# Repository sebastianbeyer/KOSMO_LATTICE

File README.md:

## KOSMO format adoption from Mutable Instruments Grids

Using the Schematic of Mutable Instruments and initial Kicad files by www.quinie.nl

I had to fix the pot direction and the button but now it works!
Remember to adjust the LED resistors (`R37, R38, R39`) to the LEDs your are using!
For the firmware I have added the compiled firmware (`grids.hex`) and a script on how to upload it to your nano (`upload.sh`, you need to adjust the paths)

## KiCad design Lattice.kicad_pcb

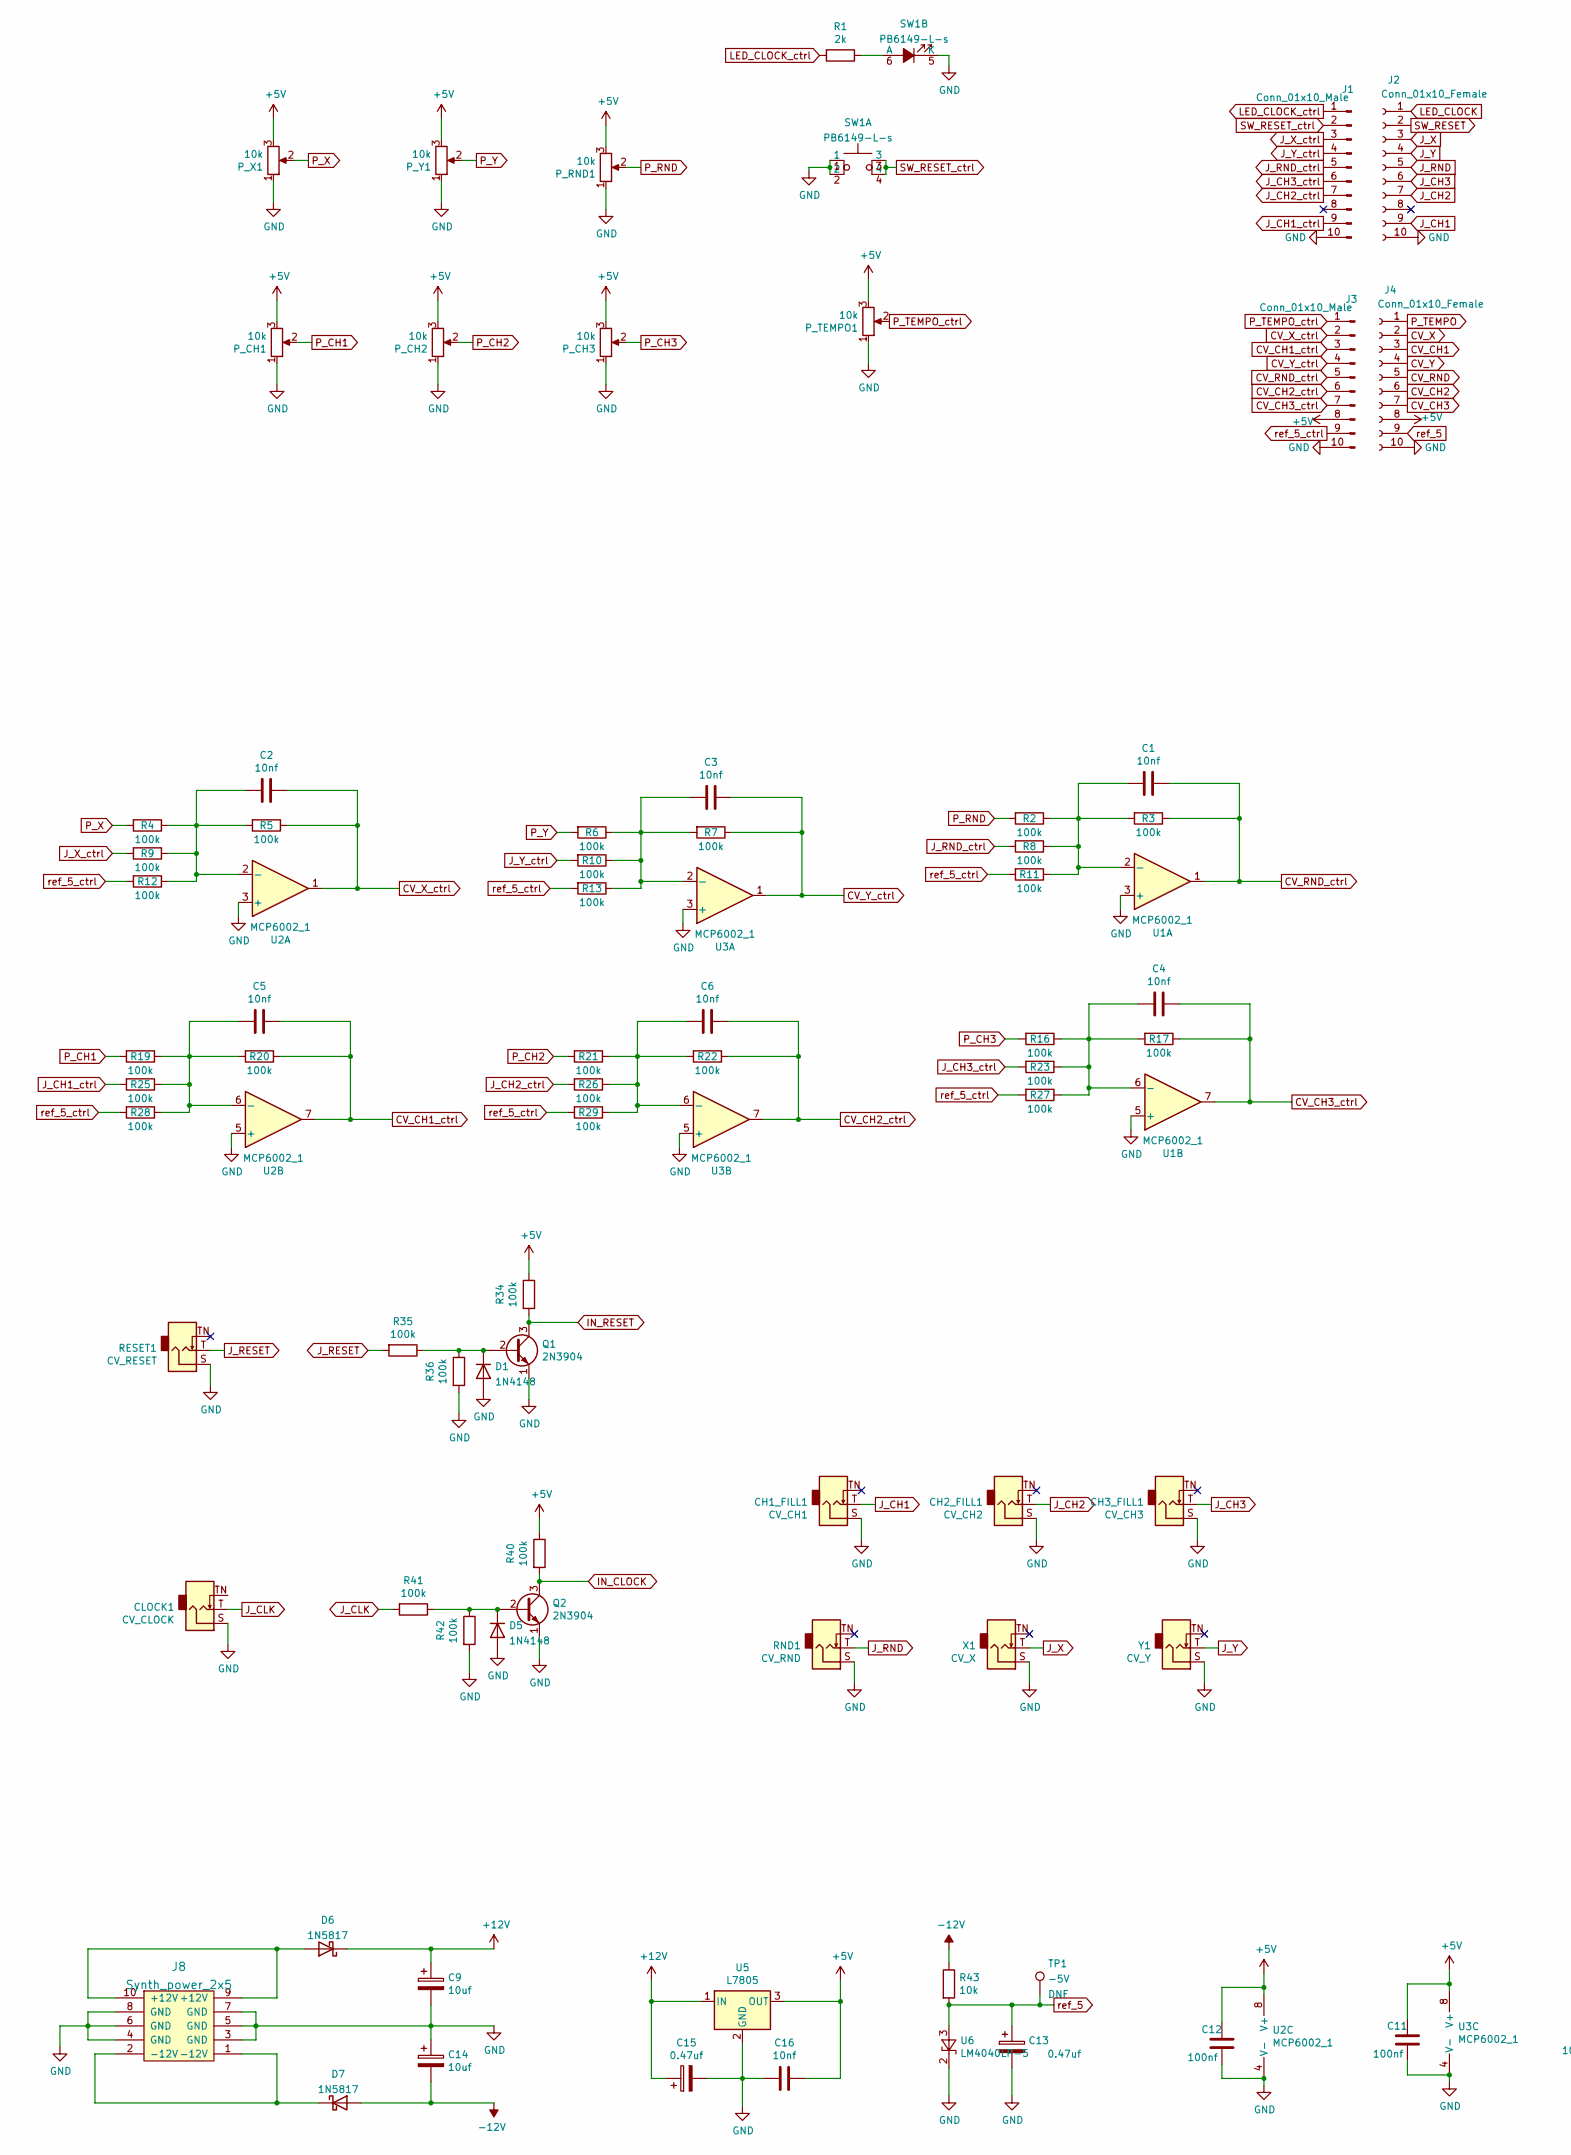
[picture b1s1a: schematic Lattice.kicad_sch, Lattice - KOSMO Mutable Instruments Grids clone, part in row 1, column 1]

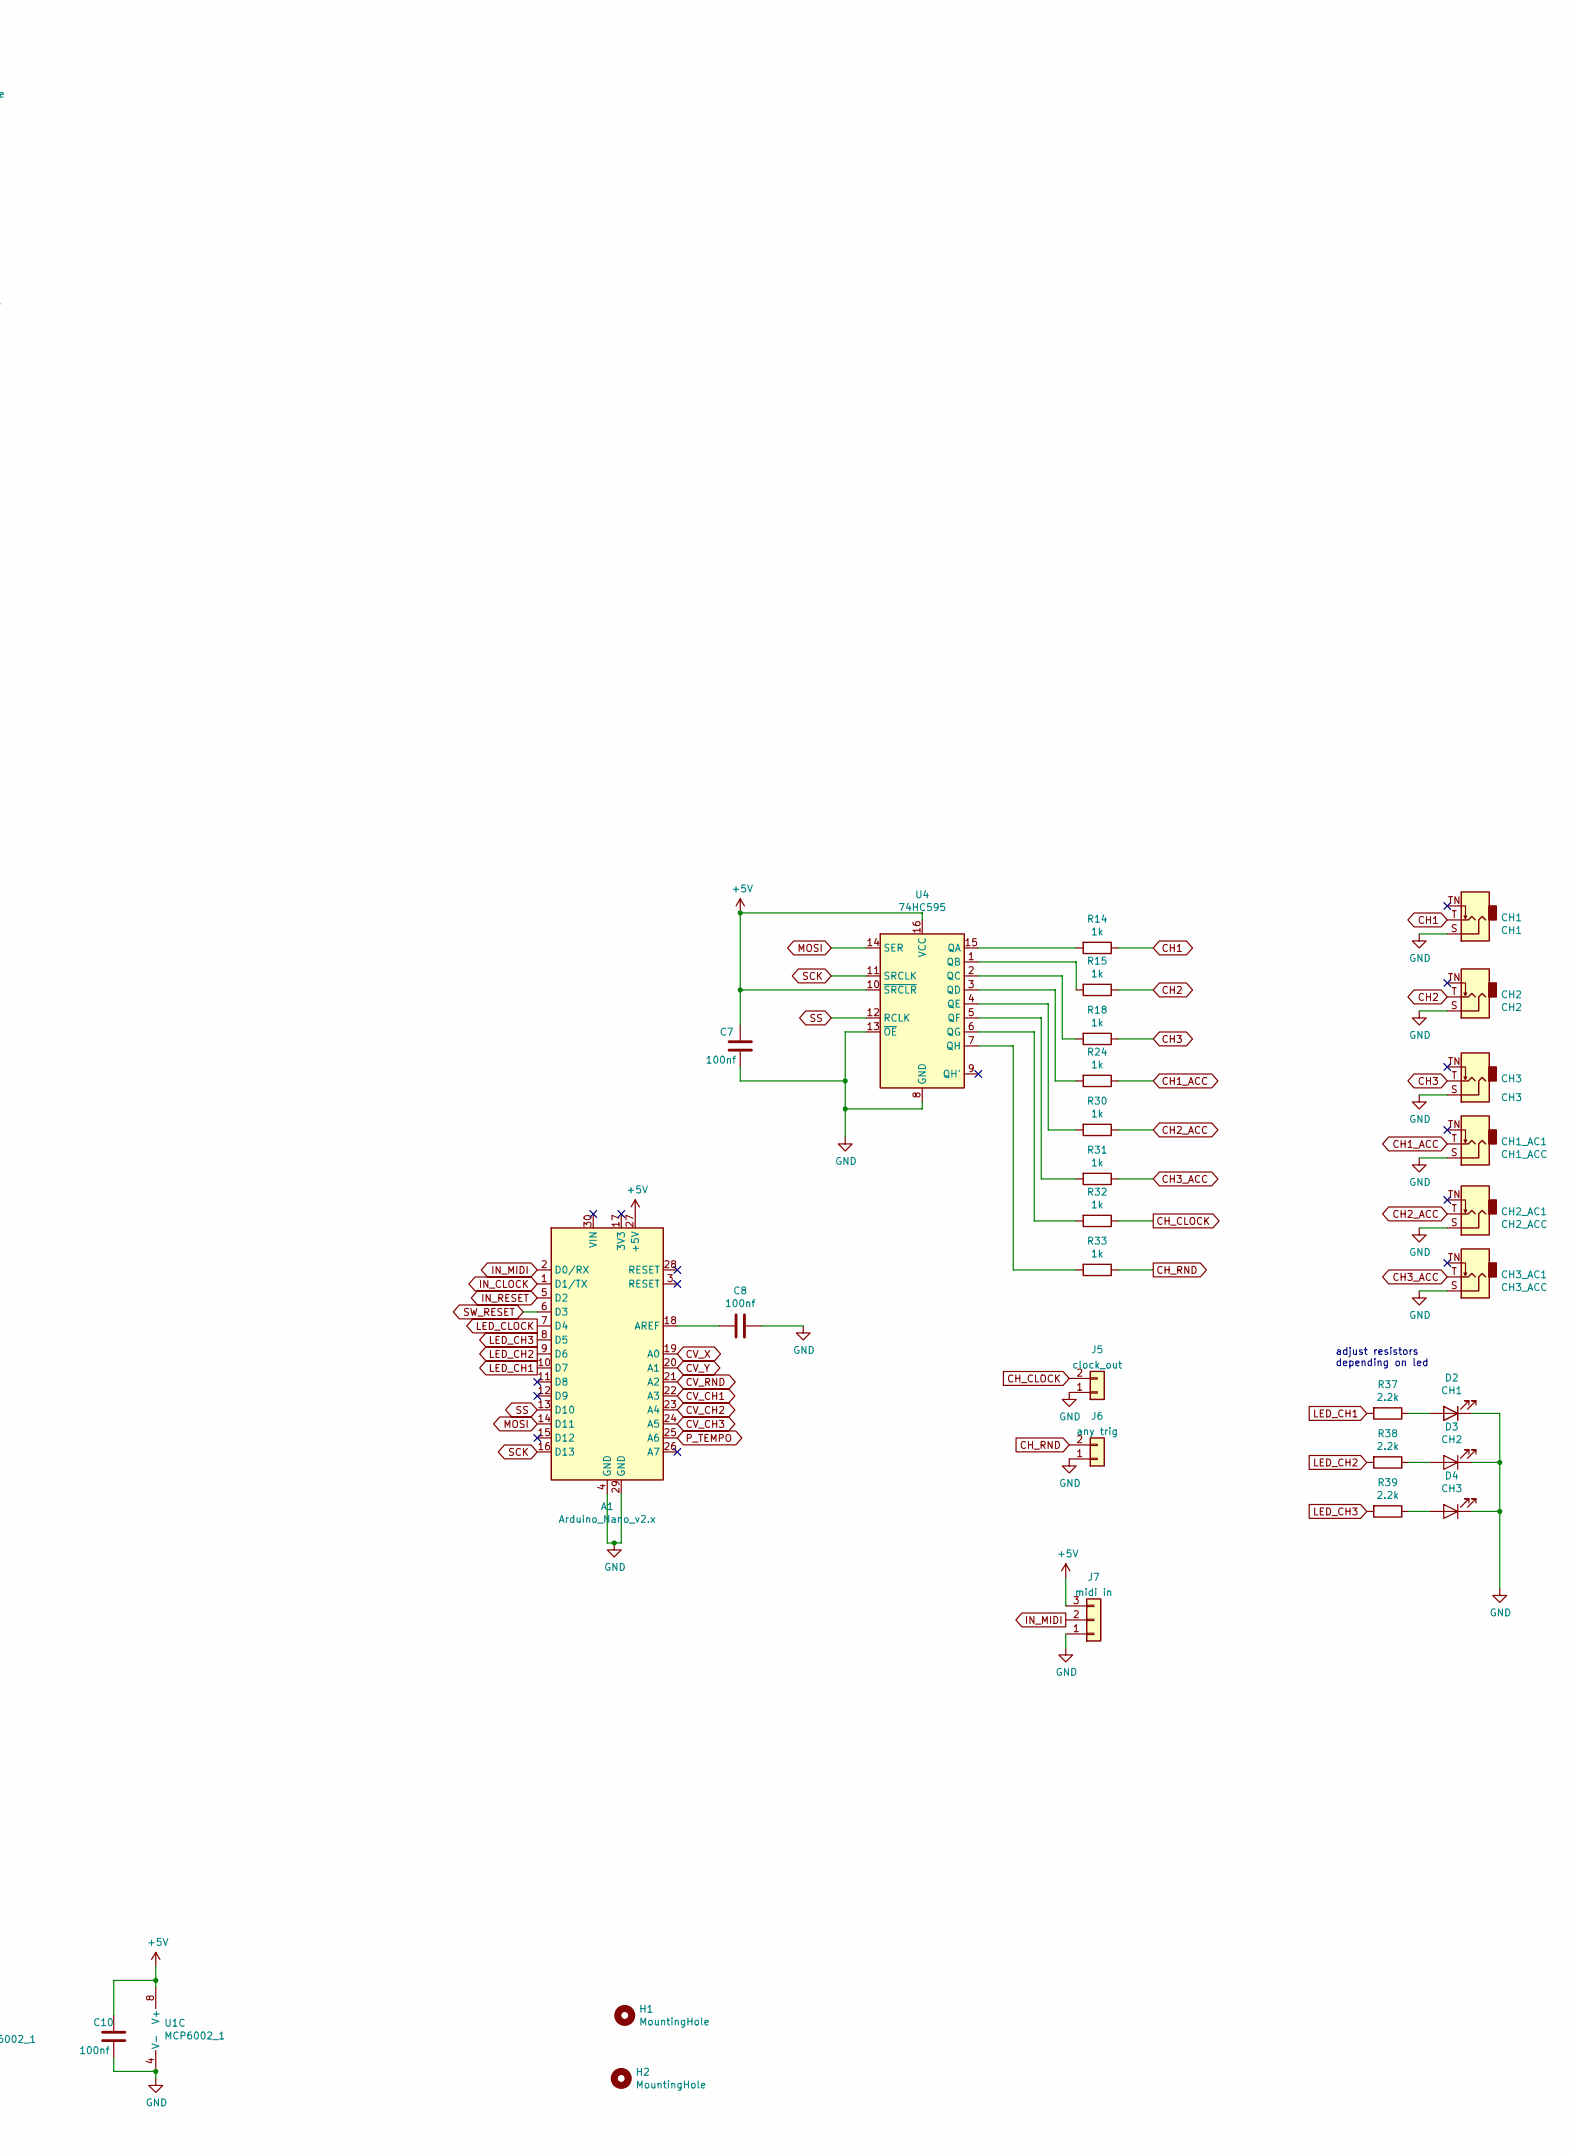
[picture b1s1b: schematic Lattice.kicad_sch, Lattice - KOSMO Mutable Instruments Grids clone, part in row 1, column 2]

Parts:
A1: Arduino_Nano_v2.x; Arduino_Nano
C1, C2, C3, C4, C5, C6, C16: 10nf; C_Disc_D3.0mm_W1.6mm_P2.50mm
C7, C8, C10, C11, C12: 100nf; C_Disc_D3.0mm_W1.6mm_P2.50mm
C9, C14: 10uf; CP_Radial_horizontalflat_D5mm_P2.50mm_H10mm_south
C13, C15: 0.47uf; CP_Radial_horizontalflat_D5mm_P2.50mm_H10mm_south
CH1: CH1; Jack_6.35mm_PJ_629HAN
CH1_AC1: CH1_ACC; Jack_6.35mm_PJ_629HAN
CH1_FILL1: CV_CH1; Jack_6.35mm_PJ_629HAN
CH2: CH2; Jack_6.35mm_PJ_629HAN
CH2_AC1: CH2_ACC; Jack_6.35mm_PJ_629HAN
CH2_FILL1: CV_CH2; Jack_6.35mm_PJ_629HAN
CH3: CH3; Jack_6.35mm_PJ_629HAN
CH3_AC1: CH3_ACC; Jack_6.35mm_PJ_629HAN
CH3_FILL1: CV_CH3; Jack_6.35mm_PJ_629HAN
CLOCK1: CV_CLOCK; Jack_6.35mm_PJ_629HAN
D1, D5: 1N4148; D_DO-35_SOD27_P7.62mm_Horizontal
D2: CH1; LED_D3.0mm
D3: CH2; LED_D3.0mm
D4: CH3; LED_D3.0mm
D6, D7: 1N5817; D_DO-41_SOD81_P10.16mm_Horizontal
H1, H2: MountingHole; MountingHole_3.2mm_M3
J1, J3: Conn_01x10_Male; PinHeader_1x10_P2.54mm_Vertical
J2, J4: Conn_01x10_Female; PinSocket_1x10_P2.54mm_Vertical
J5: clock_out; Molex_KK-254_AE-6410-02A_1x02_P2.54mm_Vertical
J6: any trig; Molex_KK-254_AE-6410-02A_1x02_P2.54mm_Vertical
J7: midi in; Molex_KK-254_AE-6410-03A_1x03_P2.54mm_Vertical
J8: Synth_power_2x5; Power_Header
P_CH1, P_CH2, P_CH3: 10k; Potentiometer_Alpha_RD901F-40-00D_Single_Vertical_centered
P_RND1: 10k; Potentiometer_Alpha_RD901F-40-00D_Single_Vertical_centered
P_TEMPO1: 10k; Potentiometer_Alpha_RD901F-40-00D_Single_Vertical_centered
P_X1: 10k; Potentiometer_Alpha_RD901F-40-00D_Single_Vertical_centered
P_Y1: 10k; Potentiometer_Alpha_RD901F-40-00D_Single_Vertical_centered
Q1, Q2: 2N3904; TO-92_Inline_Wide
R1: 2k; R_Axial_DIN0207_L6.3mm_D2.5mm_P10.16mm_Horizontal
R2, R3, R4, R5, R6, R7, R8, R9, R10, R11, R12, R13, R16, R17, R19, R20, R21, R22, R23, R25, R26, R27, R28, R29, R34, R35, R36, R40, R41, R42: 100k; R_Axial_DIN0207_L6.3mm_D2.5mm_P10.16mm_Horizontal
R14, R15, R18, R24, R30, R31, R32, R33: 1k; R_Axial_DIN0207_L6.3mm_D2.5mm_P10.16mm_Horizontal
R37, R38, R39: 2.2k; R_Axial_DIN0207_L6.3mm_D2.5mm_P10.16mm_Horizontal
R43: 10k; R_Axial_DIN0207_L6.3mm_D2.5mm_P10.16mm_Horizontal
RESET1: CV_RESET; Jack_6.35mm_PJ_629HAN
RND1: CV_RND; Jack_6.35mm_PJ_629HAN
SW1: PB6149-L-s; HIGHLY_PB6149L
TP1: -5V; TestPoint_THTPad_D1.5mm_Drill0.7mm
U1, U2, U3: MCP6002_1; DIP-8_W7.62mm_Socket_LongPads
U4: 74HC595; DIP-16_W7.62mm_Socket_LongPads
U5: L7805; TO-220-3_Horizontal_TabDown
U6: LM4040LP-5; TO-92_Inline_Wide
X1: CV_X; Jack_6.35mm_PJ_629HAN
Y1: CV_Y; Jack_6.35mm_PJ_629HAN

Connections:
+5V: A1.27 (+5V), C7.1, C10.1, C11.1, C12.1, C16.1, J3.8, J4.8, J7.3, P_CH1.3, P_CH2.3, P_CH3.3, P_RND1.3, P_TEMPO1.3, P_X1.3, P_Y1.3, R34.1, R40.1, U1.8 (V+), U2.8 (V+), U3.8 (V+), U4.10 (~SRCLR), U4.16 (VCC), U5.3 (OUT)
+12V: C9.1, C15.1, D6.1 (K), U5.1 (IN)
-12V: C14.2, D7.2 (A), R43.1
CH1: CH1.T, R14.1
CH1_ACC: CH1_AC1.T, R24.1
CH2: CH2.T, R15.1
CH2_ACC: CH2_AC1.T, R30.1
CH3: CH3.T, R18.1
CH3_ACC: CH3_AC1.T, R31.1
CH_CLOCK: J5.2, R32.1
CH_RND: J6.2, R33.1
CV_CH1: A1.22 (A3), J4.3
CV_CH1_ctrl: C5.1, J3.3, R20.1, U2.7
CV_CH2: A1.23 (A4), J4.6
CV_CH2_ctrl: C6.1, J3.6, R22.1, U3.7
CV_CH3: A1.24 (A5), J4.7
CV_CH3_ctrl: C4.1, J3.7, R17.1, U1.7
CV_RND: A1.21 (A2), J4.5
CV_RND_ctrl: C1.1, J3.5, R3.1, U1.1
CV_X: A1.19 (A0), J4.2
CV_X_ctrl: C2.1, J3.2, R5.1, U2.1
CV_Y: A1.20 (A1), J4.4
CV_Y_ctrl: C3.1, J3.4, R7.1, U3.1
GND: A1.4 (GND), A1.29 (GND), C7.2, C8.1, C9.2, C10.2, C11.2, C12.2, C13.2, C14.1, C15.2, C16.2, CH1.S, CH1_AC1.S, CH1_FILL1.S, CH2.S, CH2_AC1.S, CH2_FILL1.S, CH3.S, CH3_AC1.S, CH3_FILL1.S, CLOCK1.S, D1.2 (A), D2.1 (K), D3.1 (K), D4.1 (K), D5.2 (A), J1.10, J2.10, J3.10, J4.10, J5.1, J6.1, J7.1, J8.3 (GND), J8.4 (GND), J8.5 (GND), J8.6 (GND), J8.7 (GND), J8.8 (GND), P_CH1.1, P_CH2.1, P_CH3.1, P_RND1.1, P_TEMPO1.1, P_X1.1, P_Y1.1, Q1.1 (E), Q2.1 (E), R36.2, R42.2, RESET1.S, RND1.S, SW1.1, SW1.2, SW1.5 (K), U1.3 (+), U1.4 (V-), U1.5 (+), U2.3 (+), U2.4 (V-), U2.5 (+), U3.3 (+), U3.4 (V-), U3.5 (+), U4.8 (GND), U4.13 (~OE), U5.2 (GND), U6.2 (K), X1.S, Y1.S; also elsewhere on the board
IN_CLOCK: A1.1 (D1/TX), Q2.3 (C), R40.2
IN_MIDI: A1.2 (D0/RX), J7.2
IN_RESET: A1.5 (D2), Q1.3 (C), R34.2
J_CH1: CH1_FILL1.T, J2.9
J_CH1_ctrl: J1.9, R25.2
J_CH2: CH2_FILL1.T, J2.7
J_CH2_ctrl: J1.7, R26.2
J_CH3: CH3_FILL1.T, J2.6
J_CH3_ctrl: J1.6, R23.2
J_CLK: CLOCK1.T, R41.2
J_RESET: R35.2, RESET1.T
J_RND: J2.5, RND1.T
J_RND_ctrl: J1.5, R8.2
J_X: J2.3, X1.T
J_X_ctrl: J1.3, R9.2
J_Y: J2.4, Y1.T
J_Y_ctrl: J1.4, R10.2
LED_CH1: A1.10 (D7), R37.2
LED_CH2: A1.9 (D6), R38.2
LED_CH3: A1.8 (D5), R39.2
LED_CLOCK: A1.7 (D4), J2.1
LED_CLOCK_ctrl: J1.1, R1.2
MOSI: A1.14 (D11), U4.14 (SER)
unnamed: A1.18 (AREF), C8.2
unnamed: C1.2, R2.1, R3.2, R8.1, R11.1, U1.2 (-)
unnamed: C2.2, R4.1, R5.2, R9.1, R12.1, U2.2 (-)
unnamed: C3.2, R6.1, R7.2, R10.1, R13.1, U3.2 (-)
unnamed: C4.2, R16.1, R17.2, R23.1, R27.1, U1.6 (-)
unnamed: C5.2, R19.1, R20.2, R25.1, R28.1, U2.6 (-)
unnamed: C6.2, R21.1, R22.2, R26.1, R29.1, U3.6 (-)
unnamed: D1.1 (K), Q1.2 (B), R35.1, R36.1
unnamed: D2.2 (A), R37.1
unnamed: D3.2 (A), R38.1
unnamed: D4.2 (A), R39.1
unnamed: D5.1 (K), Q2.2 (B), R41.1, R42.1
unnamed: D6.2 (A), J8.9 (+12V), J8.10 (+12V)
unnamed: D7.1 (K), J8.1 (-12V), J8.2 (-12V)
unnamed: R1.1, SW1.6 (A)
unnamed: R14.2, U4.15 (QA)
unnamed: R15.2, U4.1 (QB)
unnamed: R18.2, U4.2 (QC)
unnamed: R24.2, U4.3 (QD)
unnamed: R30.2, U4.4 (QE)
unnamed: R31.2, U4.5 (QF)
unnamed: R32.2, U4.6 (QG)
unnamed: R33.2, U4.7 (QH)
P_CH1: P_CH1.2, R19.2
P_CH2: P_CH2.2, R21.2
P_CH3: P_CH3.2, R16.2
P_RND: P_RND1.2, R2.2
P_TEMPO: A1.25 (A6), J4.1
P_TEMPO_ctrl: J3.1, P_TEMPO1.2
P_X: P_X1.2, R4.2
P_Y: P_Y1.2, R6.2
SCK: A1.16 (D13), U4.11 (SRCLK)
SS: A1.13 (D10), U4.12 (RCLK)
SW_RESET: A1.6 (D3), J2.2
SW_RESET_ctrl: J1.2, SW1.3, SW1.4
ref_5: C13.1, J4.9, R43.2, TP1.1, U6.3 (A)
ref_5_ctrl: J3.9, R11.2, R12.2, R13.2, R27.2, R28.2, R29.2

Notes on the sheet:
adjust resistors depending on led

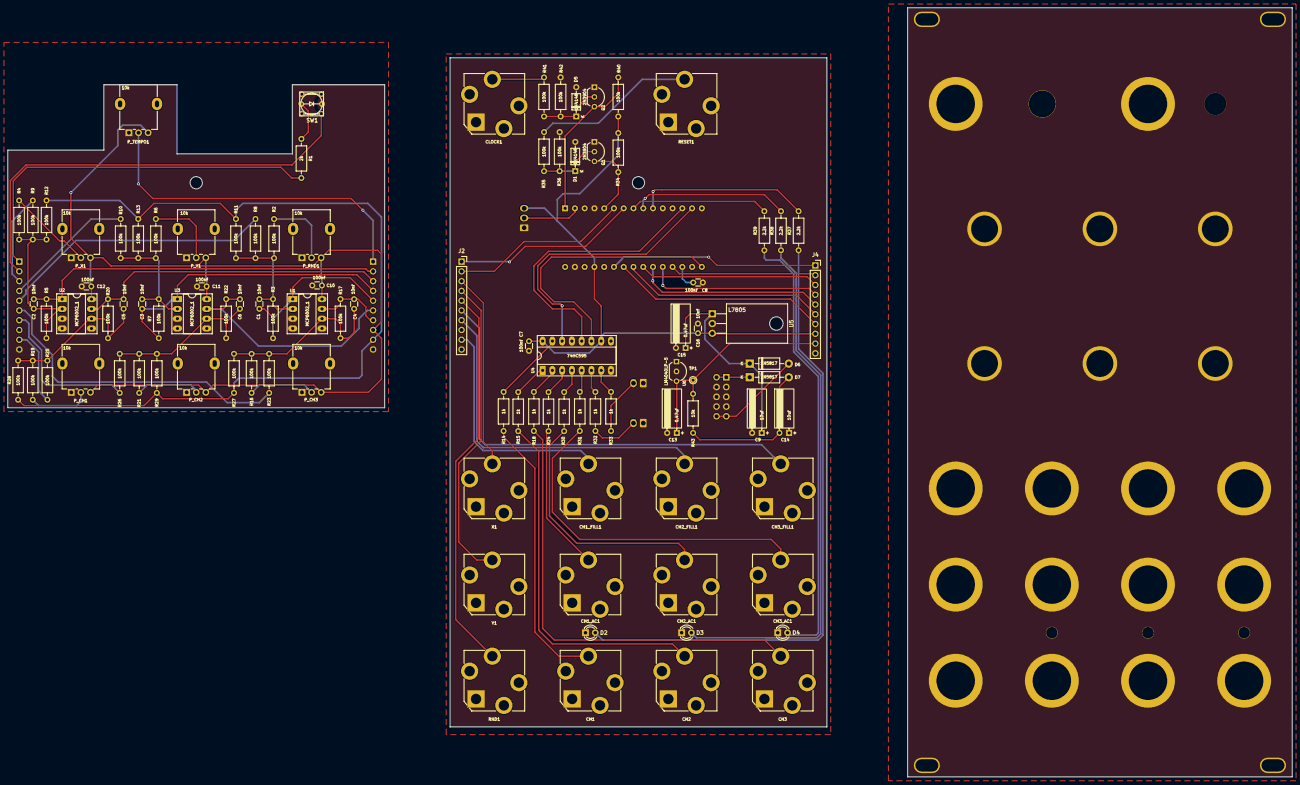
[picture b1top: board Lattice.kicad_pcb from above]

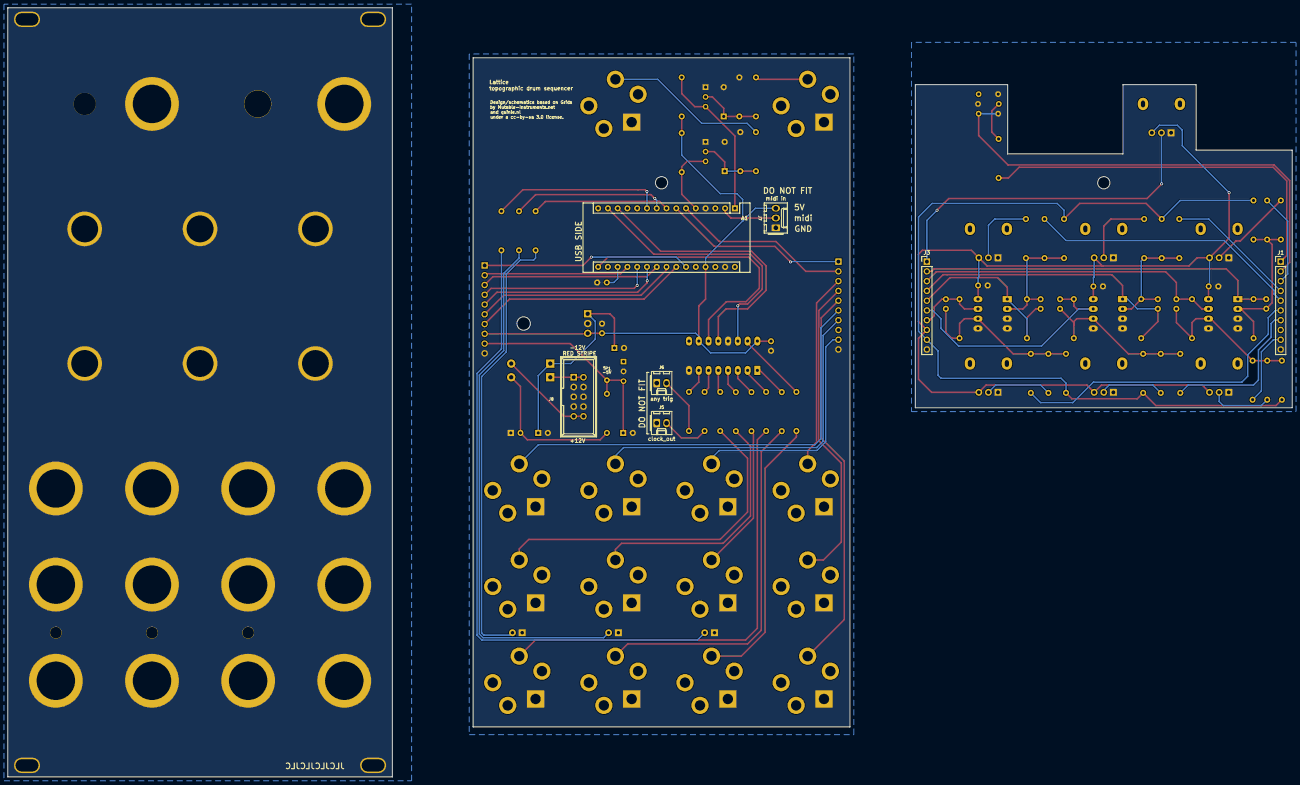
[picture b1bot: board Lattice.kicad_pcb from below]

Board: 2 copper layers, 334.0 x 200.0 mm, 109 parts (7 on the bottom side), 84 nets.

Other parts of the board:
H25: led; Kosmo_HIGHLY_PB6149L

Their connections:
GND: H25.1; also elsewhere on the board

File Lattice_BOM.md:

# Lattice.kicad_sch BOM

Tue 13 Dec 2022 10:29:21 CET

Generated from schematic by Eeschema 6.0.8-f2edbf62ab~116~ubuntu22.04.1

**Component Count:** 107

| Refs | Qty | Component | Description | Vendor | SKU |
| ----- | --- | ---- | ----------- | ---- | ---- |
| A1 | 1 | Arduino_Nano_v2.x |  |  |  |
| C1, C2, C3, C4, C5, C6, C16 | 7 | 10nf |  |  |  |
| C7, C8, C10, C11, C12 | 5 | 100nf |  |  |  |
| C9, C14 | 2 | 10uf |  |  |  |
| C13, C15 | 2 | 0.47uf |  |  |  |
| CH1 | 1 | CH1 | Audio Jack, 2 Poles (Mono / TS), Switched T Pole (Normalling) | Tayda | A-1121 |
| CH1_AC1 | 1 | CH1_ACC | Audio Jack, 2 Poles (Mono / TS), Switched T Pole (Normalling) | Tayda | A-1121 |
| CH1_FILL1 | 1 | CV_CH1 | Audio Jack, 2 Poles (Mono / TS), Switched T Pole (Normalling) | Tayda | A-1121 |
| CH2 | 1 | CH2 | Audio Jack, 2 Poles (Mono / TS), Switched T Pole (Normalling) | Tayda | A-1121 |
| CH2_AC1 | 1 | CH2_ACC | Audio Jack, 2 Poles (Mono / TS), Switched T Pole (Normalling) | Tayda | A-1121 |
| CH2_FILL1 | 1 | CV_CH2 | Audio Jack, 2 Poles (Mono / TS), Switched T Pole (Normalling) | Tayda | A-1121 |
| CH3 | 1 | CH3 | Audio Jack, 2 Poles (Mono / TS), Switched T Pole (Normalling) | Tayda | A-1121 |
| CH3_AC1 | 1 | CH3_ACC | Audio Jack, 2 Poles (Mono / TS), Switched T Pole (Normalling) | Tayda | A-1121 |
| CH3_FILL1 | 1 | CV_CH3 | Audio Jack, 2 Poles (Mono / TS), Switched T Pole (Normalling) | Tayda | A-1121 |
| CLOCK1 | 1 | CV_CLOCK | Audio Jack, 2 Poles (Mono / TS), Switched T Pole (Normalling) | Tayda | A-1121 |
| D1, D5 | 2 | 1N4148 | Standard switching diode, DO-35 | Tayda | A-157 |
| D2 | 1 | CH1 | Light emitting diode |  |  |
| D3 | 1 | CH2 |  |  |  |
| D4 | 1 | CH3 |  |  |  |
| D6, D7 | 2 | 1N5817 | Schottky Barrier Rectifier Diode, DO-41 | Tayda | A-159 |
| H1, H2 | 2 | MountingHole |  |  |  |
| J1, J3 | 2 | Conn_01x10_Male | Generic connector, single row, 01x10, script generated (kicad-library-utils/schlib/autogen/connector/) |  |  |
| J2, J4 | 2 | Conn_01x10_Female | Generic connector, single row, 01x10, script generated (kicad-library-utils/schlib/autogen/connector/) |  |  |
| J5 | 1 | clock_out | KK254 Molex header | Tayda | A-804 |
| J6 | 1 | any trig | KK254 Molex header | Tayda | A-804 |
| J7 | 1 | midi in | KK254 Molex header | Tayda | A-805 |
| J8 | 1 | Synth_power_2x5 | Pin header 2.54 mm 2x5 | Tayda | A-2939 |
| P_CH1, P_CH2, P_CH3, P_RND1, P_TEMPO1, P_X1, P_Y1 | 7 | 10k |  |  |  |
| Q1, Q2 | 2 | 2N3904 |  |  |  |
| R1 | 1 | 2k |  |  |  |
| R2, R3, R4, R5, R6, R7, R8, R9, R10, R11, R12, R13, R16, R17, R19, R20, R21, R22, R23, R25, R26, R27, R28, R29, R34, R35, R36, R40, R41, R42 | 30 | 100k |  |  |  |
| R14, R15, R18, R24, R30, R31, R32, R33 | 8 | 1k |  |  |  |
| R37, R38, R39 | 3 | 2.2k |  |  |  |
| R43 | 1 | 10k |  |  |  |
| RESET1 | 1 | CV_RESET | Audio Jack, 2 Poles (Mono / TS), Switched T Pole (Normalling) | Tayda | A-1121 |
| RND1 | 1 | CV_RND | Audio Jack, 2 Poles (Mono / TS), Switched T Pole (Normalling) | Tayda | A-1121 |
| SW1 | 1 | PB6149-L-s |  |  |  |
| U1, U2, U3 | 3 | MCP6002_1 |  |  |  |
| U4 | 1 | 74HC595 |  |  |  |
| U5 | 1 | L7805 |  |  |  |
| U6 | 1 | LM4040LP-5 |  |  |  |
| X1 | 1 | CV_X | Audio Jack, 2 Poles (Mono / TS), Switched T Pole (Normalling) | Tayda | A-1121 |
| Y1 | 1 | CV_Y | Audio Jack, 2 Poles (Mono / TS), Switched T Pole (Normalling) | Tayda | A-1121 |

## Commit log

2022-07-13 add panel render image
2022-09-12 fix pot direction
2022-11-14 fix button
2022-11-14 add upload script
2022-11-14 add firmware image
2022-11-14 update readme and add photo
2022-11-14 add note on LED resistors
2022-12-13 add bom
2022-12-13 rename bom
2023-03-19 add another upload line

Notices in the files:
Lattice.kicad_pcb:
under a cc-by-sa 3.0 license.
